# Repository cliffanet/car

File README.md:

# Проект "детская машинка"

Рассчитан на детей в качестве развлекающего и обущающего материала.

Может быть использован в разработке сторонних arduino-подобных проектах.

- [видео 1](https://disk.yandex.ru/d/IK6FT8vPRshmdA/IMG_3110.MOV)
- [видео 2](https://disk.yandex.ru/d/IK6FT8vPRshmdA/IMG_3111.MOV)

## Инструкция пользователя

Машинка катается в двух режимах:

1. Прямолинейный.

    Запускается одной из четырёх кнопок курсора:

    - вперёд,
    - назад,
    - вращение влево,
    - вращение вправо.

    Машинка будет двигаться 40 секунд и потом отключится.

    Вручную остановить её можно кнопкой "стоп", расположенной отдельно справа.

2. Программируемый.

    Нажимая непрерывно на экран пальцем или стилусом, двигаем палец
    про планируемому маршруту.

    Маршрут указан промежуточными точками. Чем быстрее двигаем пальцем-стилусом,
    тем длиннее будут прямолинейные участки.

    После отпускания пальца/стилуса от экрана, запустится таймер, по истечении
    которого машинка начнёт движение по маршруту.

    Машинка остановится при достижении конечной точки маршрута.

    Вручную остановить её можно кнопкой "стоп", расположенной отдельно справа.

> При отсутствии движения машинки и нажатия на кнопки управления
> машинка через 40 секунд перейдёт в спящий режим.
>
> Выход из спящего режима происходит при нажатии на любую кнопку управления.

## Компиляция (сборка) прошивки с помощью CubeMX

Необходимые пакеты и программы:

- [STM32CubeMX](https://www.st.com/en/development-tools/stm32cubemx.html)

- [arm-none-eabi-gcc](https://developer.arm.com/downloads/-/gnu-rm)

    Для MacOS используйте:

    ```
    brew install --cask gcc-arm-embedded
    ```

- утилита make

Исходный код находится в директории [cube](cube).

1. Открываем файл [car.stm32f401ret.ioc](cube/car.stm32f401ret.ioc) в CubeMX.

2. Жмём кнопку "Generate Code".

3. Запускаем командную строку (терминал).

4. Переходим в директорию, где лежит файл car.stm32f401ret.ioc, открытый в п.1.

5. Выполняем:

    ```
    make
    ```

6. Если всё скомпилировалось успешно, во вложенной директории build будет лежать файл car.stm32f401ret.bin

[Инструкция по обновлению прошивки](doc/fwburn/README.md)

## Изготовление платы

- [Архив с gerber-файлами](hw/v1.0/car.v.1.0.zip)

- [Схема принципиальная](hw/v1.0/car.v1.0.jpg)

## Изготовление и сборка корпуса

Комплектация:

- [Шасси](model/car-chassis.stl)

- [Кабина](model/car-cabine.stl)

- [Крепления моторов](model/car-motoclip.stl) - 4шт

Дополнительно требуется приобрести:

- Комплект "колесо-мотор" для Arduino-машины в количестве 4шт.

- [Крепёж](model/bolt.md)

## Известные проблемы

- без конденсаторов на двигателях часто подвисает

    - иногда подвисает только дисплей, достаточно остановить и дождаться ухода в сон
    - иногда подвисает напрочь, помогает только общий ребут

    Наличие керамических конденсаторов на двигателях не решает проблему полностью.

- калибровка угла поворота не учитывает разряд аккумулятора

    при более разряженном аккумуляторе поворот на тот же угол требует больше времени

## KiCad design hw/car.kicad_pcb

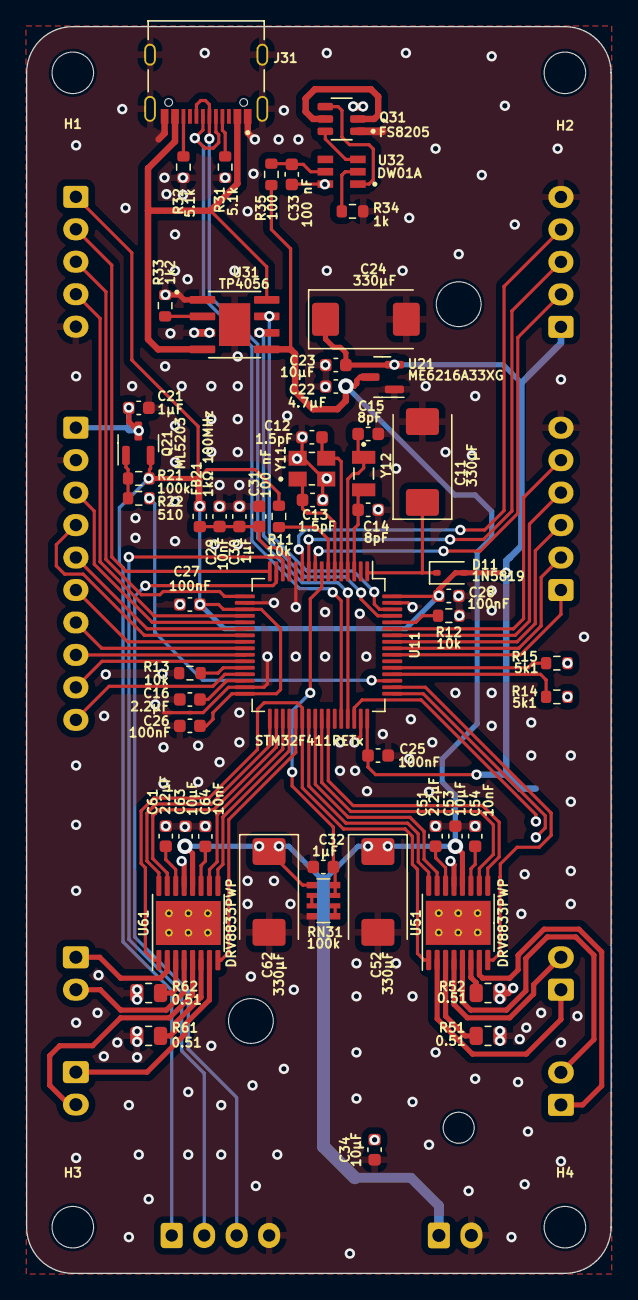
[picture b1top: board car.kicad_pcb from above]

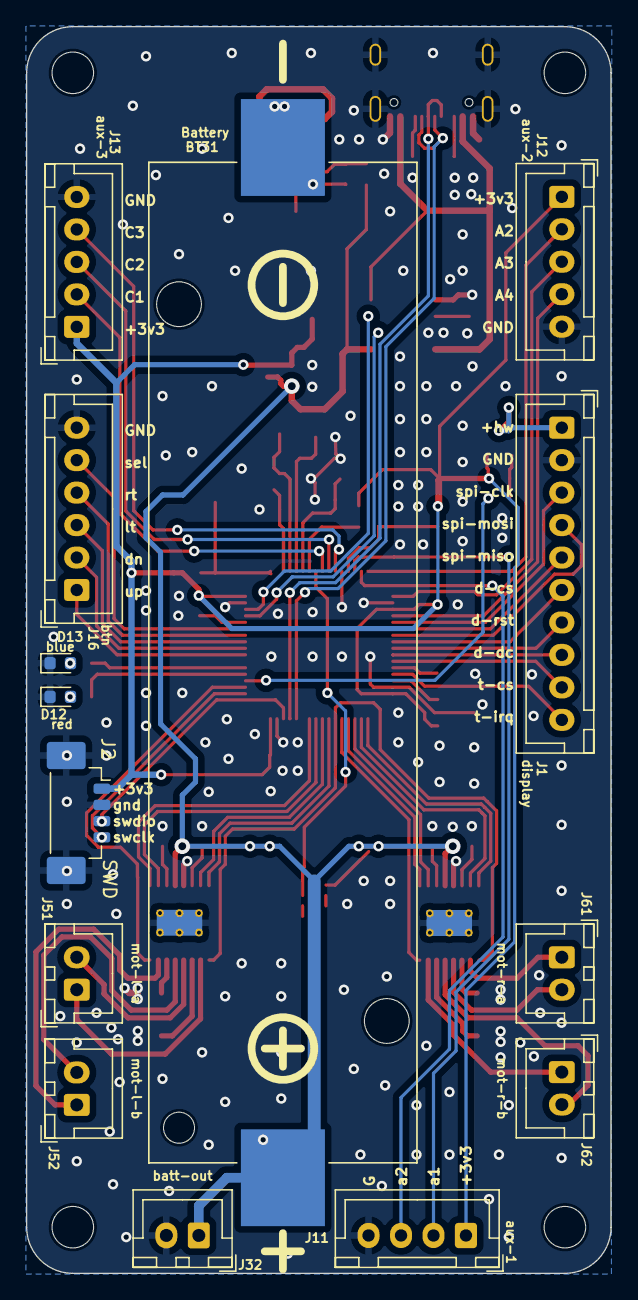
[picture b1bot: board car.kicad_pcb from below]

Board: 2 copper layers, 45.0 x 96.0 mm, 76 parts (14 on the bottom side), 87 nets.

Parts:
BT31: Battery; BAT_1042
C11, C24, C52, C62: 330μF; CP_EIA-7343-20_Kemet-V
C12, C13: 1.5pF; C_0603_1608Metric
C14, C15: 8pF; C_0603_1608Metric
C16, C51, C61: 2.2μF; C_0603_1608Metric
C21, C30, C32: 1μF; C_0603_1608Metric
C22: 4.7μF; C_0603_1608Metric
C23, C34, C53, C63: 10μF; C_0603_1608Metric
C25, C26, C27, C28: 100nF; C_0603_1608Metric
C29, C54, C64: 10nF; C_0603_1608Metric
C31, C33: 100 nF; C_0603_1608Metric
D11: 1N5819; D_SOD-323
D12: red; LED_0603_1608Metric
D13: blue; LED_0603_1608Metric
FB21: 1kΩ 100MHz; L_0603_1608Metric
H1, H2, H3, H4: MountingHole; MountingHole_3.2mm_M3
J1: display; JST_XH_B10B-XH-A_1x10_P2.50mm_Vertical
J2: SWD; Molex_PicoBlade_53398-0471_1x04-1MP_P1.25mm_Vertical
J11: aux-1; JST_XH_B4B-XH-A_1x04_P2.50mm_Vertical
J12: aux-2; JST_XH_B5B-XH-A_1x05_P2.50mm_Vertical
J13: aux-3; JST_XH_B5B-XH-A_1x05_P2.50mm_Vertical
J16: btn; JST_XH_B6B-XH-A_1x06_P2.50mm_Vertical
J31: TYPE-C-31-M-12; HRO_TYPE-C-31-M-12
J32: batt-out; JST_XH_B2B-XH-A_1x02_P2.50mm_Vertical
J51: mot-l-a; JST_XH_B2B-XH-A_1x02_P2.50mm_Vertical
J52: mot-l-b; JST_XH_B2B-XH-A_1x02_P2.50mm_Vertical
J61: mot-r-a; JST_XH_B2B-XH-A_1x02_P2.50mm_Vertical
J62: mot-r-b; JST_XH_B2B-XH-A_1x02_P2.50mm_Vertical
Q21: ML5203; SOT-23
Q31: FS8205; SOT95P280X145-6N
R11, R12, R13: 10k; R_0603_1608Metric
R14, R15: 5k1; R_0603_1608Metric
R21: 100k; R_0603_1608Metric
R22: 510; R_0603_1608Metric
R31, R32: 5.1k; R_0603_1608Metric
R33: 1k2; R_0603_1608Metric
R34: 1k; R_0603_1608Metric
R35: 100; R_0603_1608Metric
R51, R52, R61, R62: 0.51; R_0805_2012Metric
RN31: 100k; R_Array_Convex_4x0603
U11: STM32F411RETx; LQFP-64_10x10mm_P0.5mm
U21: ME6216A33XG; SOT-23
U31: TP4056; SOP127P600X175-9N
U32: DW01A; SOT95P280X145-6N
U51, U61: DRV8833PWP; HTSSOP-16-1EP_4.4x5mm_P0.65mm_EP3.4x5mm_Mask2.46x2.31mm_The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
Y11: XTAL3225 25MHz; XTAL_TSX-3225_16.0000MF18X-AC3
Y12: NX3215SA 32.768K; XTAL_NX3215SA-32.768K-STD-MUA-14

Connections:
+3.3VA: C29.2, C30.2, C31.2, FB21.2, U11.13 (VDDA)
+3V3: C23.1, C24.1, C25.1, C26.1, C27.1, C28.2, D11.2 (A), FB21.1, J2.1, J11.1, J12.1, J13.1, Q21.2 (S), R11.1, R21.2, U11.19 (VDD), U11.32 (VDD), U11.48 (VDD), U11.64 (VDD), U21.2 (VO)
+BATT: BT31.P, C22.1, C34.1, C52.1, C53.1, C62.1, C63.1, J32.1, R35.2, RN31.1 (R1.1), U21.3 (VI), U31.5 (BAT), U51.12 (VM), U61.12 (VM)
/a0: J11.2, U11.14 (PA0)
/a1: J11.3, U11.15 (PA1)
/a2: J12.2, U11.16 (PA2)
/a3: J12.3, U11.17 (PA3)
/a4: J12.4, U11.20 (PA4)
/btn-dn: J16.2, U11.56 (PB4)
/btn-lt: J16.3, U11.57 (PB5)
/btn-rt: J16.4, U11.58 (PB6)
/btn-sel: J16.5, U11.59 (PB7)
/btn-up: J16.1, U11.55 (PB3)
/c1: J13.2, U11.9 (PC1)
/c2: J13.3, U11.10 (PC2)
/c3: J13.4, U11.11 (PC3)
/chg-act: U11.62 (PB9), U31.7 (~CHRG)
/chg-sb: U11.61 (PB8), U31.6 (~STDBY)
/dspl-cs: J1.6, U11.24 (PC4)
/dspl-dc: J1.8, U11.26 (PB0)
/dspl-rst: J1.7, U11.25 (PC5)
/led-b: R15.2, U11.53 (PC12)
/led-r: R14.2, U11.52 (PC11)
/mot-l-a1: U11.39 (PC8), U51.16 (AIN1)
/mot-l-a2: U11.40 (PC9), U51.15 (AIN2)
/mot-l-b1: U11.42 (PA9), U51.9 (BIN1)
/mot-l-b2: U11.41 (PA8), U51.10 (BIN2)
/mot-l-flt: U11.50 (PA15), U51.8 (nFAULT)
/mot-r-a1: U11.33 (PB12), U61.16 (AIN1)
/mot-r-a2: U11.34 (PB13), U61.15 (AIN2)
/mot-r-b1: U11.36 (PB15), U61.9 (BIN1)
/mot-r-b2: U11.35 (PB14), U61.10 (BIN2)
/mot-r-flt: U11.37 (PC6), U61.8 (nFAULT)
/mot-slp: U11.38 (PC7), U51.1 (nSLEEP), U61.1 (nSLEEP)
/spi-clk: J1.3, U11.21 (PA5)
/spi-miso: J1.5, U11.22 (PA6)
/spi-mosi: J1.4, U11.23 (PA7)
/swclk: J2.4, U11.49 (PA14)
/swdio: J2.3, U11.46 (PA13)
/tch-cs: J1.9, U11.27 (PB1)
/tch-irq: J1.10, U11.29 (PB10)
/usb-cc1: J31.A5 (CC1), R31.2
/usb-cc2: J31.B5 (CC2), R32.2
/usb-d+: J31.A6 (DP1), J31.B6 (DP2), U11.45 (PA12)
/usb-d-: J31.A7 (DN1), J31.B7 (DN2), U11.44 (PA11)
GND: C11.2, C12.1, C13.2, C14.1, C15.1, C16.2, C21.2, C22.2, C23.2, C24.2, C25.2, C26.2, C27.2, C28.1, C29.1, C30.1, C31.1, C32.1, C34.2, C51.2, C52.2, C53.2, C54.2, C61.2, C62.2, C63.2, C64.2, D12.1 (K), D13.1 (K), J1.2, J2.2, J2.MP (MountPin), J11.4, J12.5, J13.5, J16.6, J31.A1_B12 (GND), J31.B1_A12 (GND), J31.S1 (SHIELD), J31.S2 (SHIELD), J31.S3 (SHIELD), J31.S4 (SHIELD), J32.2, Q31.1, R12.1, R13.2, R31.1, R32.1, R33.2, R34.2, R51.1, R52.1, R61.1, R62.1, RN31.4 (R4.1), U11.12 (VSSA), U11.18 (VSS), U11.31 (VSS), U11.47 (VSS), U11.63 (VSS), U21.1 (GND), U31.1 (TEMP), U31.3 (GND), U31.9 (EP), U51.13 (GND), U51.17 (GND(PPAD)), U61.13 (GND), U61.17 (GND(PPAD)), Y11.2, Y11.4
unnamed: C11.1, D11.1 (K), U11.1 (VBAT)
unnamed: D12.2 (A), R14.1
unnamed: D13.2 (A), R15.1
unnamed: J51.1, U51.2 (AOUT1)
unnamed: J51.2, U51.4 (AOUT2)
unnamed: J52.1, U51.7 (BOUT1)
unnamed: J52.2, U51.5 (BOUT2)
unnamed: J61.1, U61.2 (AOUT1)
unnamed: J61.2, U61.4 (AOUT2)
unnamed: J62.1, U61.7 (BOUT1)
unnamed: J62.2, U61.5 (BOUT2)
unnamed: Q21.1 (G), R21.1, R22.1
unnamed: Q31.2, Q31.5
unnamed: RN31.2 (R2.1), RN31.3 (R3.1)
unnamed: RN31.5 (R4.2), RN31.6 (R3.2)
unnamed: R12.2, U11.60 (BOOT0)
unnamed: R11.2, U11.7 (NRST)
unnamed: R13.1, U11.28 (PB2)
unnamed: C14.2, U11.3 (PC14), Y12.2
unnamed: C15.2, U11.4 (PC15), Y12.1
unnamed: C12.2, U11.5 (PH0), Y11.3
unnamed: C13.1, U11.6 (PH1), Y11.1
unnamed: C16.1, U11.30 (VCAP1)
unnamed: R33.1, U31.2 (PROG)
unnamed: R34.1, U32.2 (CS)
unnamed: BT31.N, C33.2, Q31.3, U32.6 (GND)
unnamed: Q31.6, U32.3 (OC)
unnamed: Q31.4, U32.1 (OD)
unnamed: C33.1, R35.1, U32.5 (VCC)
unnamed: R51.2, U51.3 (AISEN)
unnamed: R52.2, U51.6 (BISEN)
unnamed: C54.1, U51.11 (VCP)
unnamed: C51.1, U51.14 (VINT)
unnamed: R61.2, U61.3 (AISEN)
unnamed: R62.2, U61.6 (BISEN)
unnamed: C64.1, U61.11 (VCP)
unnamed: C61.1, U61.14 (VINT)
batt-info: C32.2, RN31.7 (R2.2), RN31.8 (R1.2), U11.8 (PC0)
hwen: R22.2, U11.51 (PC10)
hwpwr: C21.1, J1.1, Q21.3 (D)
usb-5v: J31.A4_B9 (VBUS), J31.B4_A9 (VBUS), U31.4 (VCC), U31.8 (CE)

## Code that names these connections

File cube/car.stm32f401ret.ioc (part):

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Mcu.Name=STM32F401R(D-E)Tx
Mcu.Package=LQFP64
Mcu.UserName=STM32F401RETx
PA11.Mode=Device_Only
PA11.Signal=USB_OTG_FS_DM
PA12.Mode=Device_Only
PA12.Signal=USB_OTG_FS_DP
PA15.GPIOParameters=GPIO_PuPd,GPIO_Label
PA15.GPIO_Label=mot-l-flt
PA15.GPIO_PuPd=GPIO_PULLUP
PA15.Signal=GPIO_Input
PA2.GPIOParameters=GPIO_PuPd,GPIO_Label,GPIO_ModeDefaultEXTI
PA2.GPIO_Label=sr04 echo
PA2.GPIO_ModeDefaultEXTI=GPIO_MODE_IT_RISING_FALLING
PA2.GPIO_PuPd=GPIO_PULLDOWN
PA2.Signal=GPXTI2
PA3.GPIOParameters=GPIO_Speed,GPIO_Label
PA3.GPIO_Label=sr04 trig
PA3.GPIO_Speed=GPIO_SPEED_FREQ_HIGH
PA3.Signal=S_TIM2_CH4
PA5.Mode=Full_Duplex_Master
PA5.Signal=SPI1_SCK
PA6.Mode=Full_Duplex_Master
PA6.Signal=SPI1_MISO
PA7.Mode=Full_Duplex_Master
PA7.Signal=SPI1_MOSI
PA8.GPIOParameters=GPIO_Label
PA8.GPIO_Label=mot-l-b2
PA8.Signal=GPIO_Output
PA9.GPIOParameters=GPIO_Label
PA9.GPIO_Label=mot-l-b1
PA9.Signal=GPIO_Output
PB0.GPIOParameters=GPIO_Speed,PinState,GPIO_Label
PB0.GPIO_Label=dspl-dc
PB0.GPIO_Speed=GPIO_SPEED_FREQ_HIGH
PB0.PinState=GPIO_PIN_RESET
PB0.Signal=GPIO_Output
PB1.GPIOParameters=GPIO_Speed,PinState,GPIO_Label
PB1.GPIO_Label=touch-cs
PB1.GPIO_Speed=GPIO_SPEED_FREQ_HIGH
PB1.PinState=GPIO_PIN_SET
PB1.Signal=GPIO_Output
PB10.GPIOParameters=GPIO_Label
PB10.GPIO_Label=touch-irq
PB10.Signal=GPXTI10
PB12.GPIOParameters=GPIO_Label
PB12.GPIO_Label=mot-r-a1
PB12.Signal=GPIO_Output
PB13.GPIOParameters=GPIO_Label
PB13.GPIO_Label=mot-r-a2
PB13.Signal=GPIO_Output
PB14.GPIOParameters=GPIO_Label
PB14.GPIO_Label=mot-r-b2
PB14.Signal=GPIO_Output
PB15.GPIOParameters=GPIO_Label
PB15.GPIO_Label=mot-r-b1
PB15.Signal=GPIO_Output
PB3.GPIOParameters=GPIO_PuPd,GPIO_Label,GPIO_ModeDefaultEXTI
PB3.GPIO_Label=btn-up
PB3.GPIO_ModeDefaultEXTI=GPIO_MODE_IT_FALLING
PB3.GPIO_PuPd=GPIO_PULLUP
PB3.Signal=GPXTI3
PB4.GPIOParameters=GPIO_PuPd,GPIO_Label,GPIO_ModeDefaultEXTI
PB4.GPIO_Label=btn-dn
PB4.GPIO_ModeDefaultEXTI=GPIO_MODE_IT_FALLING
PB4.GPIO_PuPd=GPIO_PULLUP
PB4.Signal=GPXTI4
PB5.GPIOParameters=GPIO_PuPd,GPIO_Label,GPIO_ModeDefaultEXTI
PB5.GPIO_Label=btn-lt
PB5.GPIO_ModeDefaultEXTI=GPIO_MODE_IT_FALLING
PB5.GPIO_PuPd=GPIO_PULLUP
PB5.Signal=GPXTI5
PB6.GPIOParameters=GPIO_PuPd,GPIO_Label,GPIO_ModeDefaultEXTI
PB6.GPIO_Label=btn-rt
PB6.GPIO_ModeDefaultEXTI=GPIO_MODE_IT_FALLING
PB6.GPIO_PuPd=GPIO_PULLUP
PB6.Signal=GPXTI6
PB7.GPIOParameters=GPIO_PuPd,GPIO_Label,GPIO_ModeDefaultEXTI
PB7.GPIO_Label=btn-sel
PB7.GPIO_ModeDefaultEXTI=GPIO_MODE_IT_FALLING
PB7.GPIO_PuPd=GPIO_PULLUP
PB7.Signal=GPXTI7
PB8.GPIOParameters=GPIO_PuPd,GPIO_Label
PB8.GPIO_Label=batt-chg-stb
PB8.GPIO_PuPd=GPIO_PULLUP
PB8.Signal=GPIO_Input
PB9.GPIOParameters=GPIO_PuPd,GPIO_Label
PB9.GPIO_Label=batt-chg-act
PB9.GPIO_PuPd=GPIO_PULLUP
PB9.Signal=GPIO_Input
PC0.GPIOParameters=GPIO_Label
PC0.GPIO_Label=batt-info
PC0.Signal=ADCx_IN10
PC1.GPIOParameters=GPIO_Label
PC1.GPIO_Label=aux-3-c1
PC1.Signal=GPIO_Output
PC10.GPIOParameters=PinState,GPIO_Label
PC10.GPIO_Label=hwen
PC10.PinState=GPIO_PIN_SET
PC10.Signal=GPIO_Output
PC11.GPIOParameters=GPIO_Label
PC11.GPIO_Label=led-red
PC11.Signal=GPIO_Output
PC12.GPIOParameters=GPIO_Label
PC12.GPIO_Label=led-blue
PC12.Signal=GPIO_Output
PC14-OSC32_IN.Mode=LSE-External-Oscillator
PC14-OSC32_IN.Signal=RCC_OSC32_IN
PC15-OSC32_OUT.Mode=LSE-External-Oscillator
PC15-OSC32_OUT.Signal=RCC_OSC32_OUT
PC2.GPIOParameters=GPIO_Label
PC2.GPIO_Label=aux-3-c2
PC2.Signal=GPIO_Output
PC3.GPIOParameters=GPIO_Label
PC3.GPIO_Label=aux3-c3
PC3.Signal=GPIO_Output
PC4.GPIOParameters=GPIO_Speed,PinState,GPIO_Label
PC4.GPIO_Label=dspl-cs
PC4.GPIO_Speed=GPIO_SPEED_FREQ_HIGH
PC4.PinState=GPIO_PIN_SET
PC4.Signal=GPIO_Output
PC5.GPIOParameters=GPIO_Label
PC5.GPIO_Label=dspl-rst
PC5.Signal=GPIO_Output
PC6.GPIOParameters=GPIO_PuPd,GPIO_Label
PC6.GPIO_Label=mot-r-flt
PC6.GPIO_PuPd=GPIO_PULLUP
PC6.Signal=GPIO_Input
PC7.GPIOParameters=GPIO_Speed,PinState,GPIO_Label
PC7.GPIO_Label=mot-sleep
PC7.GPIO_Speed=GPIO_SPEED_FREQ_LOW
PC7.PinState=GPIO_PIN_SET
PC7.Signal=GPIO_Output
PC8.GPIOParameters=GPIO_Label
PC8.GPIO_Label=mot-l-a1
PC8.Signal=GPIO_Output
PC9.GPIOParameters=GPIO_Label
PC9.GPIO_Label=mot-l-a2
PC9.Signal=GPIO_Output
PH0\ -\ OSC_IN.Mode=HSE-External-Oscillator
PH0\ -\ OSC_IN.Signal=RCC_OSC_IN
PH1\ -\ OSC_OUT.Mode=HSE-External-Oscillator
PH1\ -\ OSC_OUT.Signal=RCC_OSC_OUT
RCC.HSE_VALUE=25000000
RCC.SYSCLKFreq_VALUE=84000000
RCC.SYSCLKSource=RCC_SYSCLKSOURCE_PLLCLK
board=custom

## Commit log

2024-12-13 модель - шасси и крепления мотора
2024-12-14 модель - доработки под плату
2024-12-18 печатная плата - осталось только доделать надписи разъёмов и перепроверить
2024-12-18 модель - описание необходимых болтов
2024-12-19 плата - надписи
2024-12-19 модель - доработки шасси и креплений мотора
2025-01-02 модель - кабина
2025-01-02 плата - архив v1
2025-01-02 fw - заготовка
2025-01-12 модель - кабина - небольшие баги и доработки
2025-01-12 fw - реорганизация кода
2025-01-15 дисплей - драйвер аппаратной части + заготовка под gfx
2025-01-16 дисплей - двойной буфер для ускорения вывода
2025-01-16 дисплей gfx - прямоугольники
2025-01-17 дисплей - небольшой рефакторинг классов
2025-01-18 дисплей gfx - окружность и скруглённые прямоугольники
2025-01-18 дисплей - функции по преобразованию цветов
2025-01-20 тачскрин
2025-01-20 реорганизация кода основнога процессинга
2025-01-22 дисплей - вывод текста, шрифты u8g2
2025-02-01 работа кнопок, перешли пинами на свою плату
2025-02-02 модули управления светодиодами и моторами
2025-02-02 контроль заряда батареи
2025-02-02 дисплей - перевернули на 180
2025-02-02 моторы - команды управления всеми двигателями сразу
2025-02-03 управление питанием
2025-02-03 движение по нарисованному маршруту
2025-02-10 небольшие доработки
2025-02-10 документация - крепёж
2025-02-10 документация
2025-02-11 плата - небольшие правки
2025-02-12 документация - изготовление платы, программирование, фото/видео
2025-04-06 модель кузова - крепление под уз датчик расстояния
2025-04-06 дальномер - средство объезда препятствий
2025-04-08 3д кабина - уз датчик препятствий
2025-04-08 баг из-за повторного использования exti3
